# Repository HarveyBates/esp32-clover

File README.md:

# esp32-clover
ESP32 Clover development board.

## Features
- [x] USB-C connector
- [x] Debugger connector for ESP-Prog
- [x] Piezo buzzer (audible feedback)
- [x] Additional ADC (2 inputs, 12-bit)
- [x] Additional IO (2 inputs/outputs with interrupt)
- [x] Additional DAC (1 channel, 8-bit)
- [x] Battery charger (single cell LiPo)
- [x] Built-in LED
- [x] Programmable button
- [x] Breadboard friendly
- [x] Small footprint (29.2 mm x 46.5 mm)

## Schematic
The devices schematic can be found [here](https://github.com/HarveyBates/esp32-clover/blob/master/electronics/esp32-clover/schematics/esp32-clover.pdf)

## Licence
This project is under the GNU LESSER GENERAL PUBLIC LICENSE as found in the LICENCE file.

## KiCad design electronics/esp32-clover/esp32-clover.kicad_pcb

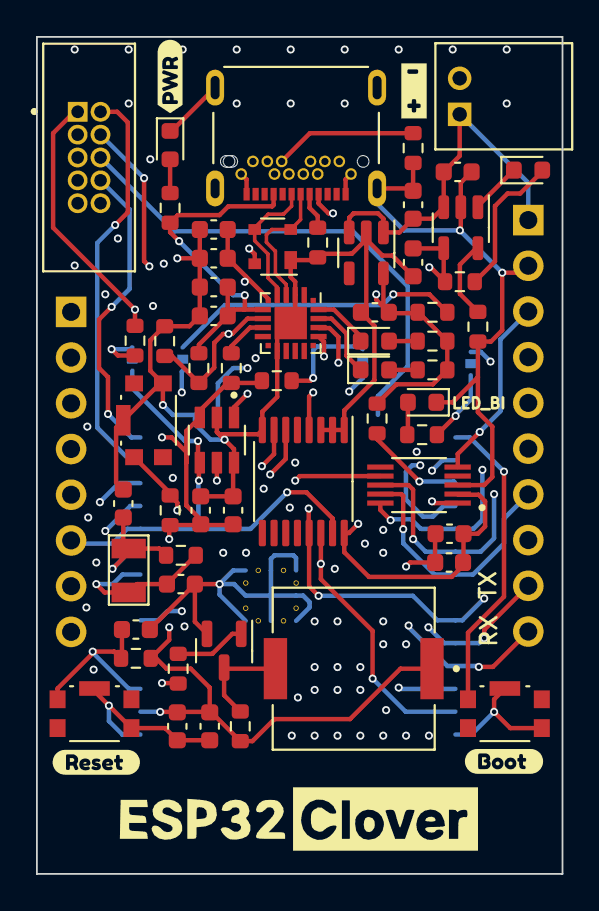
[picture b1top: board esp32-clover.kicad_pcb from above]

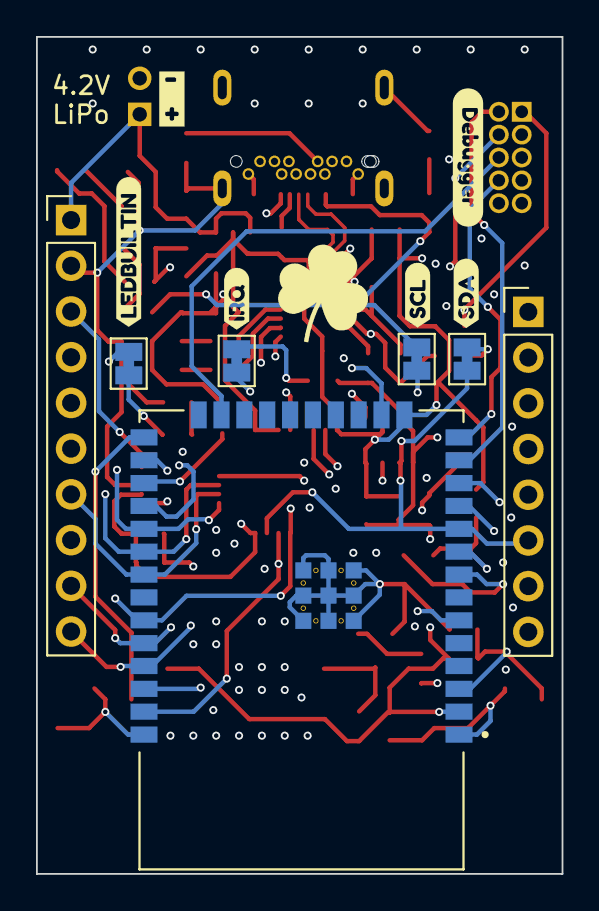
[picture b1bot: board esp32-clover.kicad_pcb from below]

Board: 4 copper layers, 29.2 x 46.5 mm, 75 parts (13 on the bottom side), 54 nets.

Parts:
C1, C2, C4, C7: 4.7uF; C_0603_1608Metric
C3, C6, C10, C15, C17: 0.1uF; C_0603_1608Metric
C5, C8, C9, C14, C16: 1uF; C_0603_1608Metric
C11: 22uF; C_0603_1608Metric
C12, C13: 12pF; C_0603_1608Metric
D1, D3, D4, D5, D6: LED; LED_0603_1608Metric
D2: SP0503BAHT; SOT-143
J1: USB4055-30-A
J2: BATT_CONN; S2B-PH-K-S_LF__SN
J3: Conn_01x08_Male; PinHeader_1x08_P2.54mm_Vertical
J4: Conn_ARM_JTAG_SWD_10; 3221-10-0100-00
J5: Conn_01x10_Male; PinHeader_1x10_P2.54mm_Vertical
JP1, JP2, JP3, JP4: SJ_B; SolderJumper-2_P1.3mm_Bridged_Pad1.0x1.5mm
LS1: PKMCS0909E4000-R1
Q1: BC847; SOT-23
R1, R7: 5.1K; R_0603_1608Metric
R2, R16, R20: 470; R_0603_1608Metric
R3: 2.5K; R_0603_1608Metric
R4: 22.1K; R_0603_1608Metric
R5: 47.5K; R_0603_1608Metric
R6, R8, R9, R18: 1K; R_0603_1608Metric
R10, R13, R17, R19: 10K; R_0603_1608Metric
R11, R14, R15: 4.7K; R_0603_1608Metric
R12: 10M; R_0603_1608Metric
SW1: RESET; MCIPTG23K-V
SW2: BOOT; MCIPTG23K-V
SW3: PROG_BTN; MCIPTG23K-V
U1: MCP73832-2-OT; SOT-23-5
U2: CP2102N-Axx-xQFN20; SiliconLabs_QFN-20-1EP_3x3mm_P0.5mm_EP1.8x1.8mm
U3: NCP163ASN330T1G; SOT-23-5
U4: ESP32-WROOM-32E_(16MB); ESP32-WROOM-32E__16MB
U5: TCA9534; TSSOP-16_4.4x5mm_P0.65mm
U6: ADC124S101CIMM
U7: DAC5571IDBVR; SOT95P280X145-6N
Y1: ABS07AIG-32.768KHZ-T
kibuzzard-6379A8C6: G***; kibuzzard-6379A8C6
kibuzzard-6379A9B5: G***; kibuzzard-6379A9B5
kibuzzard-6379A92C: G***; kibuzzard-6379A92C
kibuzzard-6379A99C: G***; kibuzzard-6379A99C
kibuzzard-6379A982: G***; kibuzzard-6379A982
kibuzzard-6379AA22: G***; kibuzzard-6379AA22
kibuzzard-6379AA41: G***; kibuzzard-6379AA41
kibuzzard-6379AB75, kibuzzard-6379AB75#2: G***; kibuzzard-6379AB75
kibuzzard-6379ABD3: G***; kibuzzard-6379ABD3

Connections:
+3.3V: C6.1, C7.1, C8.1, C10.1, C11.1, C14.1, C15.1, C16.1, C17.1, J4.1 (VTref), LS1.1, R6.2, R8.1, R9.1, R10.2, R11.2, R13.2, R14.2, R15.2, R18.2, R19.2, U2.6 (VDD), U3.5 (VOUT), U4.2 (3V3), U5.16 (VDD), U6.2 (VA), U7.3 (VDD)
/DEBUG_TCK: J4.4 (SWDCLK/TCK), U4.16 (IO13)
/DEBUG_TDI: J4.8 (NC/TDI), U4.14 (IO12)
/DEBUG_TDO: J4.6 (SWO/TDO), U4.23 (IO15)
/DEBUG_TMS: J4.2 (SWDIO/TMS), U4.13 (IO14)
/ESP32_BOOT: SW2.1, U4.25 (IO0)
/GPI34/BTN: R19.1, SW3.1, U4.6 (IO34)
/UART_RX: J5.10, U2.17 (RXD), U4.35 (TXD0)
/UART_TX: J5.9, U2.18 (TXD), U4.34 (RXD0)
/USB_D+: D2.2 (K), J1.A6 (DP1), U2.4 (D+)
/USB_D-: D2.3 (K), J1.A7 (DN1), U2.5 (D-)
/VBAT: C4.1, C5.1, J2.1, J5.1, U1.3 (VBAT), U3.1 (VIN), U3.3 (EN)
ADC_IN1: J3.2, U6.7 (IN1)
ADC_IN3: J5.3, U6.5 (IN3)
DAC_VOUT: J3.1, U7.1 (VOUT)
GND: C1.2, C2.2, C3.2, C4.2, C5.2, C6.2, C7.2, C8.2, C9.2, C10.2, C11.2, C12.2, C13.2, C14.2, C15.2, C16.2, C17.2, D2.1 (A), D5.1 (K), D6.1 (K), J1.A1 (GND1.1), J1.A12 (GND1.2), J1.B1 (GND2.1), J1.B12 (GND2.2), J1.S1 (SHIELD), J1.S2 (SHIELD), J1.S3 (SHIELD), J1.S4 (SHIELD), J2.2, J4.3 (GND), J4.5 (GND), J4.9 (GNDDetect), J5.2, Q1.2 (E), R1.1, R3.1, R5.2, R7.2, SW1.4, SW1.5, SW2.4, SW2.5, SW3.4, SW3.5, U1.2 (VSS), U2.3 (GND), U2.12 (GND), U2.21 (GND), U3.2 (GND), U4.1 (GND), U4.15 (GND), U4.38 (GND), U4.39_1 (GND), U4.39_2 (GND), U4.39_3 (GND), U4.39_4 (GND), U4.39_5 (GND), U4.39_6 (GND), U4.39_7 (GND), U4.39_8 (GND), U4.39_9 (GND), U5.1 (A0), U5.2 (A1), U5.3 (A2), U5.8 (GND), U6.3 (GND), U7.2 (GND), U7.6 (A0)
GPIO4/ADC_CS: U4.26 (IO4), U6.1 (~CS)
GPIO17: J5.4, U4.28 (IO17)
GPIO21/TCA9534_INT: J5.8, JP1.2 (B), U4.33 (IO21), U5.13 (~INT)
GPIO27/PIEZO: R17.2, U4.12 (IO27)
I2C_SCL: J3.5, JP2.1 (A), U4.37 (IO23), U5.14 (SCL), U7.5 (SCL)
I2C_SDA: J3.6, JP3.1 (A), U4.10 (IO25), U5.15 (SDA), U7.4 (SDA)
unnamed: C9.1, R10.1, SW1.1, U4.3 (EN)
unnamed: C12.1, R12.2, U4.8 (IO32), Y1.2
unnamed: C13.1, R12.1, U4.9 (IO33), Y1.1
unnamed: D1.1 (K), U1.1 (STAT)
unnamed: D1.2 (A), R2.2
unnamed: D2.4 (K), R4.2, R5.1, U2.8 (VBUS)
unnamed: D3.1 (K), U2.20 (~TXT/GPIO.2)
unnamed: D3.2 (A), R8.2
unnamed: D4.1 (K), U2.19 (~RXT/GPIO.3)
unnamed: D4.2 (A), R9.2
unnamed: D5.2 (A), R16.1
unnamed: D6.2 (A), R20.1
unnamed: J1.A5 (CC1), R1.2
unnamed: J1.B5 (CC2), R7.1
unnamed: JP1.1 (A), R11.1
unnamed: JP2.2 (B), R14.1
unnamed: JP3.2 (B), R15.1
unnamed: JP4.2 (B), R16.2
unnamed: LS1.2, Q1.3 (C), R18.1
unnamed: Q1.1 (B), R17.1
unnamed: R3.2, U1.5 (PROG)
unnamed: R6.1, U2.9 (~RST)
unnamed: R13.1, U4.27 (IO16)
SPI_MISO: J5.7, U4.31 (IO19), U6.9 (DOUT)
SPI_MOSI: J5.6, U4.30 (IO18), U6.8 (DIN)
SPI_SCK: J5.5, U4.29 (IO5), U6.10 (SCLK)
TCA9534_P0: JP4.1 (A), U5.4 (P0)
TCA9534_P2: J3.4, U5.6 (P2)
TCA9534_P3: J3.3, U5.7 (P3)
UART_RX1: J3.7, U4.11 (IO26)
UART_TX1: J3.8, U4.36 (IO22)
VBUS: C1.1, C2.1, C3.1, J1.A4 (VBUS1.1), J1.A9 (VBUS1.2), R2.1, R4.1, R20.2, U1.4 (VDD), U2.7 (VREGIN)

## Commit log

2022-11-19 initial commit of electronics
2022-11-19 added boards json configuration
2022-11-20 added pcb layout and imgs folder
2022-11-20 Create LICENCE
2022-11-20 added transfer and stitching vias, closes #1
2022-11-20 added gerber and sent first version off to be manufactured (v0.1)
2022-11-20 added schematic for v0.1
2022-12-19 added arduino variant pin definitions, still more to do
2023-07-22 update for v2
2023-08-07 update before switching to stm32

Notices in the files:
parts and their libraries:
Copyright 2021 Accelerated Designs. All rights reserved.
